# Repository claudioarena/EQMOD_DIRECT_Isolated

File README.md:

# EQMOD Direct - Isolated Serial to USB board

This is a KiCad PCB for an isolated UART to USB board.
It can be used as isolated EQDIRECT board to connect to your HEQ5 or EQ6 astronomical mount.
It can also be used as a generic, isolated UART converter board, with optional DTR and RTS lines.

If you want to make your own, or order one from JLC PCB, you can find details and the needed files below.
I also have some extra boards (both assembled and bare PCB), that I sell, at pretty much the manufacturing price. You will only need to add a USB cable, and the cable from your mount to the board (again, details below).

Price is around 10 euros assembled, and a few euros for the bare PCBs, plus shipping (shipping from Italy).
For more details, contact me at:

16009140+claudioarena@users.noreply.github.com

## Overview

The board was inspired by [this project](https://olegkutkov.me/2018/02/14/isolated-eqmod-adapter-telescope-control/).

The board uses an FT232RL IC for the serial to USB conversion, and AdUM1201AR for the isolation.
The board also has appropriate diodes for ESD protection on the USB and UART connections.
There are also some PTC/Fuse protections, and USB power filtering included.

The board can easily be used on a HEQ5, EQ6 and similar astronomy mounts, to enable pc control.
In this respect, it behaves like an EQDIRECT cable, but with extra isolations and protections.
The board can also be used, thanks to an optional AdUM1200AR, as a generic isolated UART converter board. The second isolator breaks out the DTR and RST lines.

This, together with the broken out connector, can allow the board to be used, for example, with an Arduino or an ESP32 board, were full isolation is needed.

## Using with an HEQ5/EQ6

Please refer to [this page](http://eq-mod.sourceforge.net/eqdirect2.htm) for connection details.
You want to connect the Tx pin on the board to the Rx pin on the mount, and the Rx pin on the board to the Tx pin on the mount.

Once you have connected Tx, Rx, GND and 12V from the mount to the board, and a USB cable from your PC to the board, it should all just works. The PC should remember the COM port (i.e. COM port number shouldn't change), and Windows 10 should download the appropriate drivers automatically.

## Schematics

The schematics of the board is composed of two parts, separated by the isolator chips.
On the left, we can see the USB connector and the protection diodes IC. The USB lines are then connected to the FT232RL IC. The USB 5V line is fused, filtered, and provides power to the whole left side of the board (USB side of the isolator).

The signals are then fed to the isolator chips. On the UART side of the board, we can also see a 5V regulator. This takes the 12V from the mount (or other equipment), and regulates it down to 5V for the isolator chip. This is also fused and regulated. Note that there are fuses on both the 5V and 12V lines.

The idea here is to use the board in a few possible ways:
- Provide 12V to the board on the UART side. You can then use the 5V as an output. However, the 5V regulator use can only provide very little current, so be careful. In this case, the UART will be 5V logical level.
- Provide 5V to the board on the UART side. In this can, you can leave the regulator, its protection fuse and levelling capacitor unpopulated.
- Provide a different voltage level (e.g. 3.3V) to the UART side, using the 5V connection. Provided that this is within the acceptable range of the isolator chips, this can be used to give you a different voltage levels UART.

There are also 4 indicator LEDs. Two of them indicate if power if present on either side of the board (USB power and 5V or 12V connection on the UART side). The other 2 LEDs are connected to CBUS0 and CBUS1 on the FT232RL IC. Those line normally indicate activity on the Tx and Rx line.

## PCB Images

## Make your own board

You can use the following gerber, bom and assembly files to order yourself from JLC PCB:

[gerber-jlc.zip](gerber/gerber-jlc.zip)

[EQMOD_DIRECT_Isolated-jlc.csv](bom/EQMOD_DIRECT_Isolated-jlc.csv)

[EQMOD_DIRECT_Isolated-top-jlcpcb.csv](assembly/EQMOD_DIRECT_Isolated-top-jlcpcb.csv)

If you order yourself, PLEASE VERIFY EVERYTHING LOOKS AS YOU EXPECT.
With the above files, you should get all IC correctly rotated and populated.
But maybe there are some part shortages, or part order number changed since writing this. So, double check.

The above files for assembly, are missing a few ICs.
First of all, it's missing the second isolator IC. It's a relatively expensive parts, and not needed for EQ6 boards. IF you need it, you can solder it later yourself, or add it to the assembly files.

It's also missing the fuses. You need to select yourself if you want normal fuses or Polyfuse, and of which trip current. It's also missing the inductor/ferrite bead for USB power filtering.
Again, here you need to choose which value you want.
Schematic values are, in my opinion, reasonable values, but you are free to tweak them. Easy enough to solder them after the assembly process.

You might also want to tweak the value of the LED resistor. The default 3.3k are quite bright.
For a very dim, night use, astronomy friendly LEDs, try 100k instead. 

Finally, you can both solder the USB and UART connectors, or solder wires directly to the board. There are slots cut into the PCB, if you want to solder wire directly, to add some strain relief using some zip ties.

## Testing the board

If you want to make sure your board works as expected, and works in many many different scenarios, I've written a simple script to stress test the device.
Check it out [here](https://github.com/claudioarena/Serial_stress_test).

Simply short out the Tx and Rx line on the board (so that messages sent from the board are received back), and power the UART side of the board from an external supply (either 12V or 5V connection).

The python script will run through a combinations of different serial Baud rates, and check with various lengths of random strings to see if the received messages match the outgoing ones.

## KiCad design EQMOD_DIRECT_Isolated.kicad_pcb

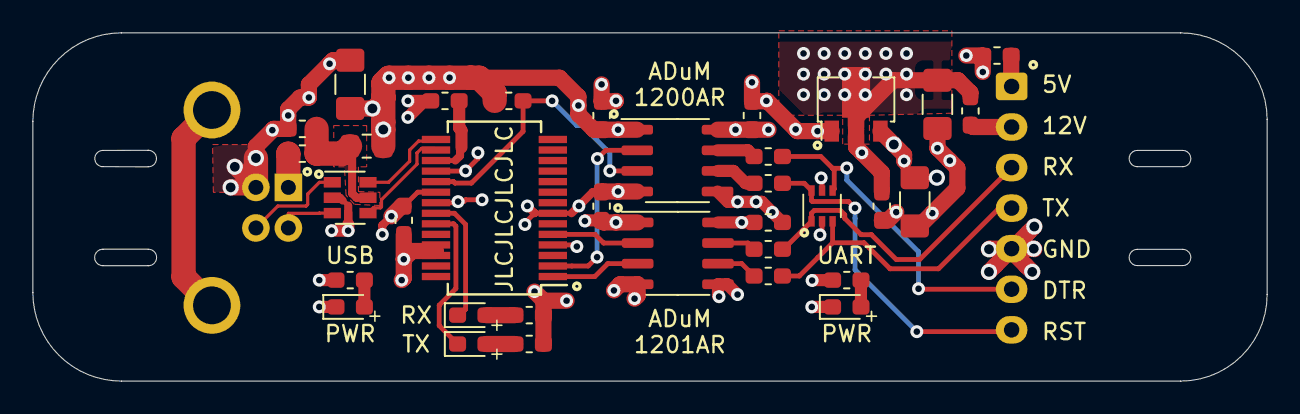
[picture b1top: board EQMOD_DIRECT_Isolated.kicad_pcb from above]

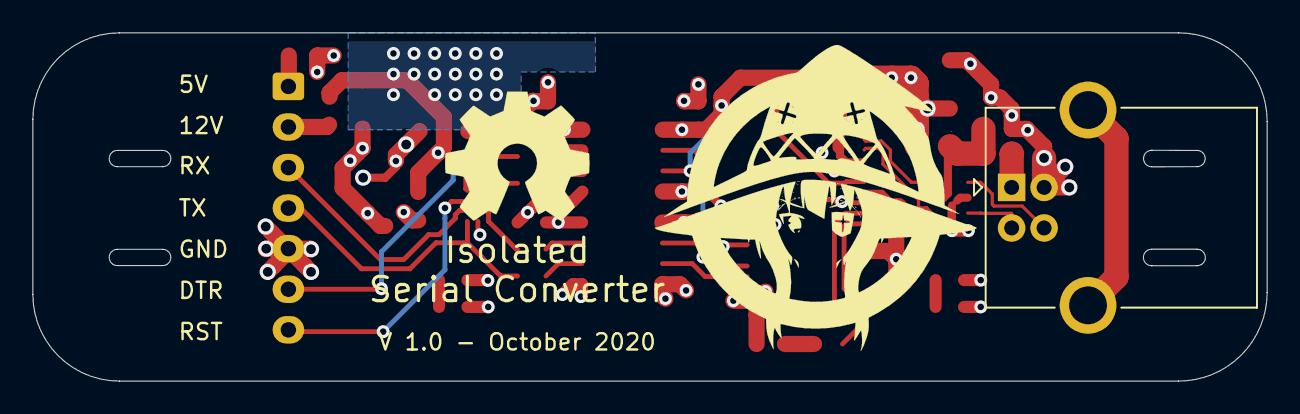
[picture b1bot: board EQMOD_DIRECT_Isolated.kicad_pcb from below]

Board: 4 copper layers, 76.1 x 21.5 mm, 36 parts (2 on the bottom side), 32 nets.

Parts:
C1, C2, C3, C5, C6, C8, C9, C10: 100 nF; C_0603_1608Metric_Pad1.05x0.95mm_HandSolder
C4, C7, C11: 4.7 uF; C_1206_3216Metric_Pad1.42x1.75mm_HandSolder
D1: LED_P_A; LED_0603_1608Metric_Pad1.05x0.95mm_HandSolder
D2: LED_P_B; LED_0603_1608Metric_Pad1.05x0.95mm_HandSolder
D3: LED_Rx; LED_0603_1608Metric_Pad1.05x0.95mm_HandSolder
D4: LED_Tx; LED_0603_1608Metric_Pad1.05x0.95mm_HandSolder
F1, F2, F3: 150 mA; Fuse_0603_1608Metric_Pad1.05x0.95mm_HandSolder
FB1: 120 @ 100 Mhz; L_0805_2012Metric_Pad1.15x1.40mm_HandSolder
J1: USB_B; USB_B_OST_USB-B1HSxx_Horizontal
J2: UART; JST_XH_B7B-XH-A_1x07_P2.50mm_Vertical_noCourtyard
R1, R2, R3, R4: 3.3k; R_0603_1608Metric_Pad1.05x0.95mm_HandSolder
R5: 10k; R_0603_1608Metric_Pad1.05x0.95mm_HandSolder
R6, R7, R8, R9: 200; R_0603_1608Metric_Pad1.05x0.95mm_HandSolder
U1: USBLC6-2SC6; SOT-23-6
U2: FT232RL; SSOP-28_5.3x10.2mm_P0.65mm
U3: ADuM1201AR; SOIC-8_3.9x4.9mm_P1.27mm
U4: ADuM1200AR; SOIC-8_3.9x4.9mm_P1.27mm
U5: NUP4202; SOT-363_SC-70-6
U6: HT7550-1-SOT89; SOT-89-3

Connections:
+5VL: C3.1, C4.1, C5.1, C6.2, FB1.1, R1.2, R3.1, R4.1, R5.1, U2.4, U2.20, U3.1, U4.1
+5VP: C7.1, C9.2, C10.2, F3.1, R2.2, U3.8, U4.8, U5.5, U6.3
/D+: J1.3, U1.1
/D-: J1.2, U1.3
/DTR: U2.2, U4.2
/DTR_PROTECTED: J2.6, R9.1, U5.4
/D_PROTECTED+: U1.6, U2.15
/D_PROTECTED-: U1.4, U2.16
/RST: R5.2, U2.19, U4.3
/RST_PROTECTED: J2.7, R6.1, U5.6
/RX: U2.5, U3.2
/RXLED: D3.1, U2.22
/RX_CONN: J2.3, R8.1, U5.1
/TX: U2.1, U3.3
/TXLED: D4.1, U2.23
/TX_CONN: J2.4, R7.1, U5.3
/V_USB: F1.1, J1.1
/V_USB_FUSED: C1.1, F1.2, FB1.2, U1.5
/Vin: C8.1, C11.1, F2.1, U6.2
GND: C7.2, C8.2, C9.1, C10.1, C11.2, D2.1, J2.5, U3.5, U4.5, U5.2, U6.1
GNDREF: C1.2, C2.2, C3.2, C4.2, C5.2, C6.1, D1.1, J1.4, U1.2, U2.7, U2.18, U2.21, U2.25, U2.26, U3.4, U4.4
unnamed: C2.1, U2.17
unnamed: D1.2, R1.1
unnamed: D2.2, R2.1
unnamed: D3.2, R3.2
unnamed: D4.2, R4.2
unnamed: F2.2, J2.2
unnamed: F3.2, J2.1
unnamed: R6.2, U4.6
unnamed: R7.2, U3.6
unnamed: R8.2, U3.7
unnamed: R9.2, U4.7

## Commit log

2021-01-10 First commit
    First commit. This is Version 1.0 of the board, which was ordered and tested in October-November 2020.
